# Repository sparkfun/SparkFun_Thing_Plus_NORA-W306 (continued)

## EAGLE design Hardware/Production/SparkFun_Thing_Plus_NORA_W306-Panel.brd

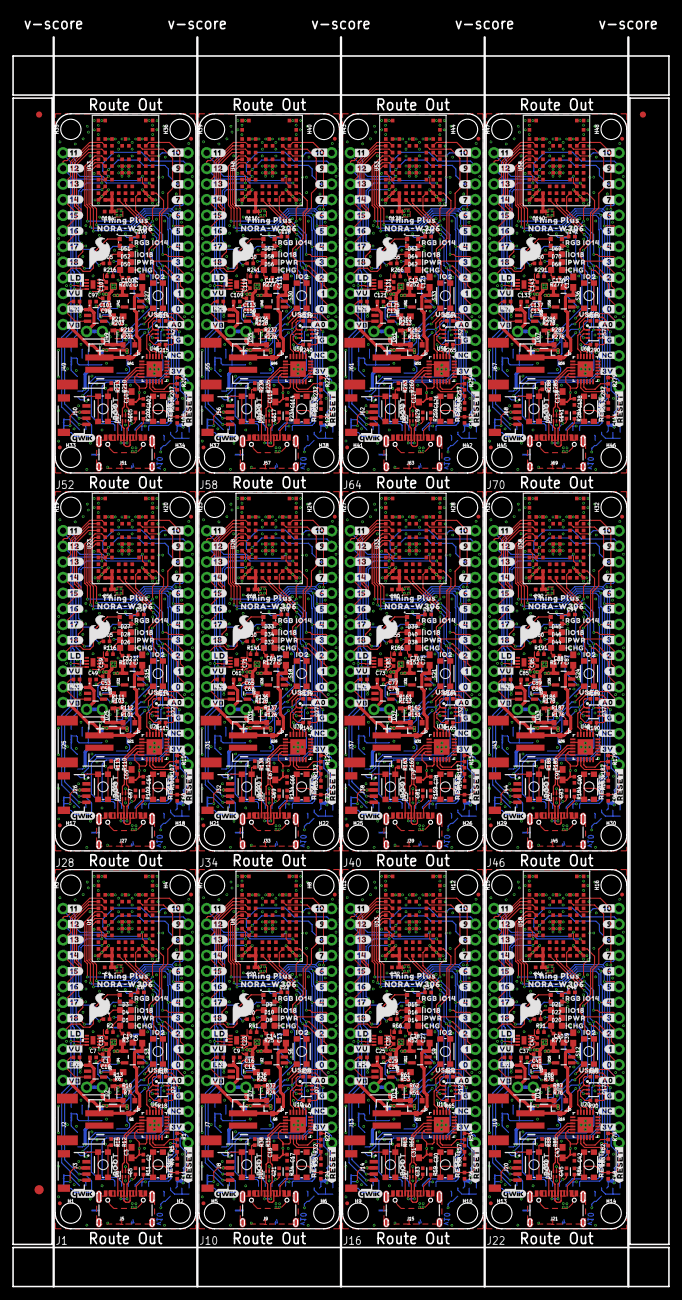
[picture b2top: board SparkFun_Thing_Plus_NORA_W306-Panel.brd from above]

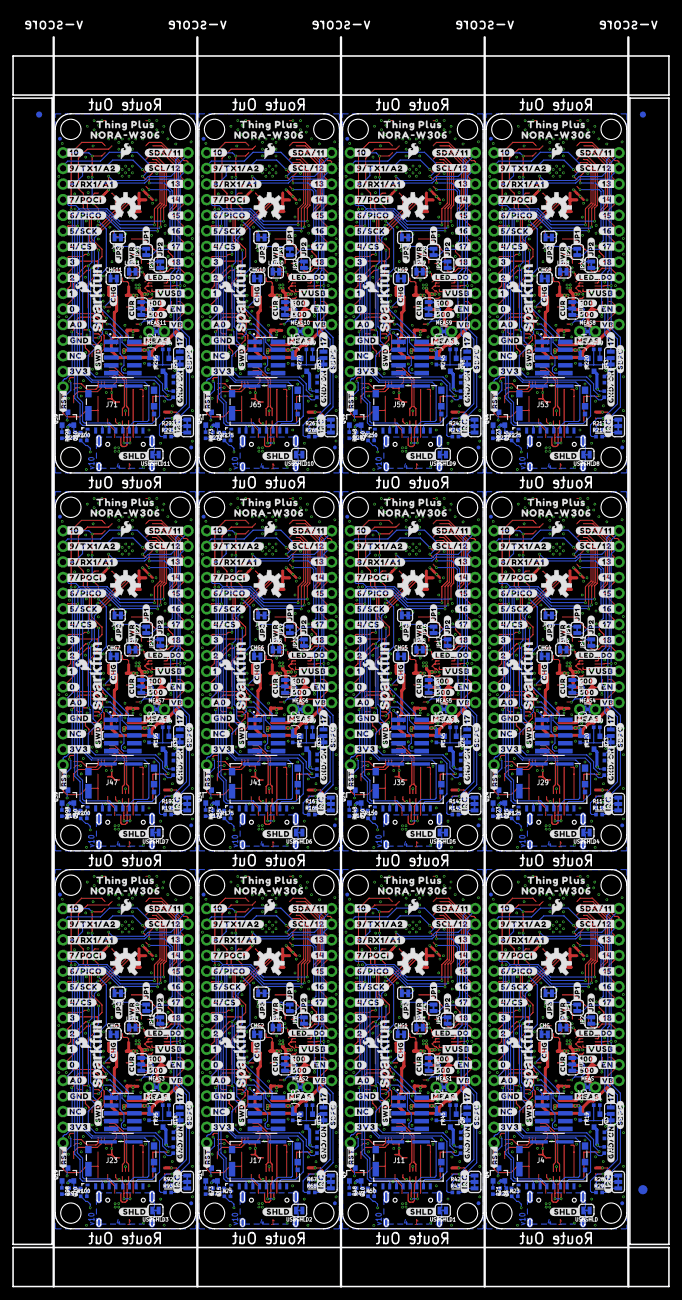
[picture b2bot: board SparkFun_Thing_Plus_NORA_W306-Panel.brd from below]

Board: 4 copper layers, 106.7 x 203.2 mm, 2022 parts (891 on the bottom side), 792 nets.

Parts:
C1, C4, C5, C16, C20, C21, C29, C32, C33, C41, C44, C45, C53, C56, C57, C65, C68, C69, C77, C80, C81, C89, C92, C93, C101, C104, C105, C113, C116, C117, C125, C128, C129, C137, C140, C141: 10uF; 0402-TIGHT
C2, C8, C11, C15, C17, C22, C23, C24, C30, C34, C35, C36, C42, C46, C47, C48, C54, C58, C59, C60, C66, C70, C71, C72, C78, C82, C83, C84, C90, C94, C95, C96, C102, C106, C107, C108, C114, C118, C119, C120, C126, C130, C131, C132, C138, C142, C143, C144: 0.1uF; 0402-TIGHT
C3, C6, C13, C14, C18, C19, C27, C28, C31, C39, C40, C43, C51, C52, C55, C63, C64, C67, C75, C76, C79, C87, C88, C91, C99, C100, C103, C111, C112, C115, C123, C124, C127, C135, C136, C139: 4.7uF; 0603
C7, C9, C10, C12, C25, C26, C37, C38, C49, C50, C61, C62, C73, C74, C85, C86, C97, C98, C109, C110, C121, C122, C133, C134: 1.0uF; 0402-TIGHT
CHG, CHG1, CHG2, CHG3, CHG4, CHG5, CHG6, CHG7, CHG8, CHG9, CHG10, CHG11: SMT-JUMPER_2_NC_TRACE_SILK
CUR, CUR1, CUR2, CUR3, CUR4, CUR5, CUR6, CUR7, CUR8, CUR9, CUR10, CUR11: SMT-JUMPER_3_1-NC_TRACE_SILK
D1, D8, D14, D20, D26, D32, D38, D44, D50, D56, D62, D68: Yellow; LED-0603
D2, D7, D13, D19, D25, D31, D37, D43, D49, D55, D61, D67: 1A/23V/620mV; SOD-323
D3, D9, D15, D21, D27, D33, D39, D45, D51, D57, D63, D69: BLUE; LED-0603
D4, D10, D16, D22, D28, D34, D40, D46, D52, D58, D64, D70: RED; LED-0603
D5, D12, D18, D24, D30, D36, D42, D48, D54, D60, D66, D72: WS2812; WS2812-2020
D6, D11, D17, D23, D29, D35, D41, D47, D53, D59, D65, D71: PRTR5V0U2F; SOT886
E$1, E$2, E$3, E$4: FIDUCIAL-1X2
E$5, E$6: FIDUCIAL-1.5X3
FD1, FD2, FD3, FD4, FD5, FD6, FD7, FD8, FD9, FD10, FD11, FD12, FD13, FD14, FD15, FD16, FD17, FD18, FD19, FD20, FD21, FD22, FD23, FD24, FD25, FD26, FD27, FD28, FD29, FD30, FD31, FD32, FD33, FD34, FD35, FD36, FD37, FD38, FD39, FD40, FD41, FD42, FD43, FD44, FD45, FD46, FD47, FD48: FIDUCIALUFIDUCIAL; FIDUCIAL-MICRO
H1, H2, H3, H4, H5, H6, H7, H8, H9, H10, H11, H12, H13, H14, H15, H16, H17, H18, H19, H20, H21, H22, H23, H24, H25, H26, H27, H28, H29, H30, H31, H32, H33, H34, H35, H36, H37, H38, H39, H40, H41, H42, H43, H44, H45, H46, H47, H48: STAND-OFF
I2C, I2C1, I2C2, I2C3, I2C4, I2C5, I2C6, I2C7, I2C8, I2C9, I2C10, I2C11: JUMPER-SMT_3_2-NC_TRACE_SILK; SMT-JUMPER_3_2-NC_TRACE_SILK
J1, J10, J16, J22, J28, J34, J40, J46, J52, J58, J64, J70: THING_PLUS_LOGICAL; THING_PLUS
J2, J7, J13, J19, J25, J31, J37, J43, J49, J55, J61, J67: LiPo; JST-2-SMD
J3, J8, J14, J20, J26, J32, J38, J44, J50, J56, J62, J68: QWIIC_RIGHT_ANGLE; JST04_1MM_RA
J4, J11, J17, J23, J29, J35, J41, J47, J53, J59, J65, J71: SDFRICTION; MICROSD_TINY
J5, J9, J15, J21, J27, J33, J39, J45, J51, J57, J63, J69: USB-C; USB-C-16P-4LAYER-ISOLATED
J6, J12, J18, J24, J30, J36, J42, J48, J54, J60, J66, J72: SWD (DNP); 2X5-SMD-UNSHROUDED_DNP_NO_PASTE
JP1, JP2, JP3, JP4, JP5, JP6, JP7, JP8, JP9, JP10, JP11, JP12, JP13, JP14, JP15, JP16, JP17, JP18, JP19, JP20, JP21, JP22, JP23, JP24, JP25, JP26, JP27, JP28, JP29, JP30, JP31, JP32, JP33, JP34, JP35, JP36: SMT-JUMPER_2_NC_TRACE_SILK
LED, LED1, LED2, LED3, LED4, LED5, LED6, LED7, LED8, LED9, LED10, LED11: SMT-JUMPER_2_NC_TRACE_SILK
LOGO1, LOGO2, LOGO7, LOGO10, LOGO13, LOGO16, LOGO19, LOGO22, LOGO25, LOGO28, LOGO31, LOGO34: OSHW-LOGOM; OSHW-LOGO-M
LOGO3, LOGO5, LOGO9, LOGO12, LOGO15, LOGO18, LOGO21, LOGO24, LOGO27, LOGO30, LOGO33, LOGO36: SFE_LOGO_NAME_FLAME.1_INCH; SFE_LOGO_NAME_FLAME_.1
LOGO4, LOGO6, LOGO8, LOGO11, LOGO14, LOGO17, LOGO20, LOGO23, LOGO26, LOGO29, LOGO32, LOGO35: QWIIC_LOGO_4MM; QWIIC_4MM
MEAS, MEAS1, MEAS2, MEAS3, MEAS4, MEAS5, MEAS6, MEAS7, MEAS8, MEAS9, MEAS10, MEAS11: COMBO-JUMPER_2_NC_TRACE
Q1, Q3, Q4, Q6, Q8, Q9, Q11, Q13, Q14, Q16, Q18, Q19, Q21, Q23, Q24, Q26, Q28, Q29, Q31, Q33, Q34, Q36, Q38, Q39, Q41, Q43, Q44, Q46, Q48, Q49, Q51, Q53, Q54, Q56, Q58, Q59: 20V/4.2A/52mΩ/1.4W; SOT23-3
Q2, Q7, Q12, Q17, Q22, Q27, Q32, Q37, Q42, Q47, Q52, Q57: MBT3904DW1T1; SC70-6
Q5, Q10, Q15, Q20, Q25, Q30, Q35, Q40, Q45, Q50, Q55, Q60: 20V/0.2A/8MHz/1.2Ω/1Vth; SOT-416FL
R1, R13, R17, R18, R27, R36, R39, R40, R54, R61, R64, R65, R79, R86, R89, R90, R104, R111, R114, R115, R129, R136, R139, R140, R154, R161, R164, R165, R179, R186, R189, R190, R204, R211, R214, R215, R229, R236, R239, R240, R254, R261, R264, R265, R279, R286, R289, R290: 10k; 0402-TIGHT
R2, R3, R4, R25, R30, R41, R52, R55, R66, R77, R80, R91, R102, R105, R116, R127, R130, R141, R152, R155, R166, R177, R180, R191, R202, R205, R216, R227, R230, R241, R252, R255, R266, R277, R280, R291: 4.7k; 0402-TIGHT
R5, R32, R57, R82, R107, R132, R157, R182, R207, R232, R257, R282: 22k; 0402-TIGHT
R6, R26, R53, R78, R103, R128, R153, R178, R203, R228, R253, R278: 2.0k; 0603
R7, R8, R16, R19, R20, R24, R31, R45, R46, R47, R51, R56, R70, R71, R72, R76, R81, R95, R96, R97, R101, R106, R120, R121, R122, R126, R131, R145, R146, R147, R151, R156, R170, R171, R172, R176, R181, R195, R196, R197, R201, R206, R220, R221, R222, R226, R231, R245, R246, R247, R251, R256, R270, R271, R272, R276, R281, R295, R296, R297: 100k; 0402-TIGHT
R9, R33, R58, R83, R108, R133, R158, R183, R208, R233, R258, R283: 33k; 0402-TIGHT
R10, R14, R21, R23, R37, R44, R48, R50, R62, R69, R73, R75, R87, R94, R98, R100, R112, R119, R123, R125, R137, R144, R148, R150, R162, R169, R173, R175, R187, R194, R198, R200, R212, R219, R223, R225, R237, R244, R248, R250, R262, R269, R273, R275, R287, R294, R298, R300: 100; 0402-TIGHT
R11, R12, R34, R35, R59, R60, R84, R85, R109, R110, R134, R135, R159, R160, R184, R185, R209, R210, R234, R235, R259, R260, R284, R285: 5.1k; 0402-TIGHT
R15, R22, R38, R49, R63, R74, R88, R99, R113, R124, R138, R149, R163, R174, R188, R199, R213, R224, R238, R249, R263, R274, R288, R299: 1k; 0402-TIGHT
R28, R29, R42, R43, R67, R68, R92, R93, R117, R118, R142, R143, R167, R168, R192, R193, R217, R218, R242, R243, R267, R268, R292, R293: 2.2k; 0402-TIGHT
S1, S4, S7, S10, S13, S16, S19, S22, S25, S28, S31, S34: RESET; TACTILE_SWITCH_SMD_4.6X2.8MM
S2, S5, S8, S11, S14, S17, S20, S23, S26, S29, S32, S35: BOOT; TACTILE_SWITCH_SMD_4.6X2.8MM
S3, S6, S9, S12, S15, S18, S21, S24, S27, S30, S33, S36: USER; TACTILE_SWITCH_SMD_4.6X2.8MM
SDPC, SDPC1, SDPC2, SDPC3, SDPC4, SDPC5, SDPC6, SDPC7, SDPC8, SDPC9, SDPC10, SDPC11: SMT-JUMPER_3_1-NC_TRACE_SILK
U1, U8, U13, U18, U23, U28, U33, U38, U43, U48, U53, U58: UBLOX_NORA_W306; UBLOX-NORA-W3
U2, U4, U11, U16, U21, U26, U31, U36, U41, U46, U51, U56: MCP73831; SOT23-5
U3, U7, U12, U17, U22, U27, U32, U37, U42, U47, U52, U57: XC6222B331MR-G; SOT23-5
U5, U9, U14, U19, U24, U29, U34, U39, U44, U49, U54, U59: MAX17048; DFN-8
U6, U10, U15, U20, U25, U30, U35, U40, U45, U50, U55, U60: CP2102N; QFN24
U$1, U$22, U$132, U$161, U$217, U$246, U$302, U$331, U$387, U$416, U$472, U$501, U$557, U$586, U$642, U$671, U$727, U$756, U$812, U$841, U$897, U$926, U$982, U$1011: #17#11
U$2, U$92, U$177, U$262, U$347, U$432, U$517, U$602, U$687, U$772, U$857, U$942: BOOT0
U$3, U$157, U$242, U$327, U$412, U$497, U$582, U$667, U$752, U$837, U$922, U$1007: #MEAS#1714141838
U$4, U$166, U$251, U$336, U$421, U$506, U$591, U$676, U$761, U$846, U$931, U$1016: IO180
U$5, U$94, U$179, U$264, U$349, U$434, U$519, U$604, U$689, U$774, U$859, U$944: NORA#W3060
U$6, U$162, U$247, U$332, U$417, U$502, U$587, U$672, U$757, U$842, U$927, U$1012: ##RST##23061714141845
U$7, U$123, U$208, U$293, U$378, U$463, U$548, U$633, U$718, U$803, U$888, U$973: USER0
U$8, U$95, U$180, U$265, U$350, U$435, U$520, U$605, U$690, U$775, U$860, U$945: SFE_LOGO_FLAME_.2
U$9, U$167, U$252, U$337, U$422, U$507, U$592, U$677, U$762, U$847, U$932, U$1017: IO20
U$10, U$160, U$245, U$330, U$415, U$500, U$585, U$670, U$755, U$840, U$925, U$1010: #GND#ON#3061714141842
U$11, U$170, U$255, U$340, U$425, U$510, U$595, U$680, U$765, U$850, U$935, U$1020: #SDPC#0
U$12, U$96, U$181, U$266, U$351, U$436, U$521, U$606, U$691, U$776, U$861, U$946: #A0#1
U$13, U$150, U$235, U$320, U$405, U$490, U$575, U$660, U$745, U$830, U$915, U$1000: #SDA#11#28
U$14, U$152, U$237, U$322, U$407, U$492, U$577, U$662, U$747, U$832, U$917, U$1002: #17#28
U$15, U$97, U$182, U$267, U$352, U$437, U$522, U$607, U$692, U$777, U$862, U$947: #0#4
U$16, U$98, U$183, U$268, U$353, U$438, U$523, U$608, U$693, U$778, U$863, U$948: #1#4
U$17, U$151, U$236, U$321, U$406, U$491, U$576, U$661, U$746, U$831, U$916, U$1001: #SCL#12#28
U$18, U$153, U$238, U$323, U$408, U$493, U$578, U$663, U$748, U$833, U$918, U$1003: #18#28
U$19, U$154, U$239, U$324, U$409, U$494, U$579, U$664, U$749, U$834, U$919, U$1004: SFE_LOGO_FLAME_.1
U$20, U$155, U$240, U$325, U$410, U$495, U$580, U$665, U$750, U$835, U$920, U$1005: #LD#29
U$21, U$168, U$253, U$338, U$423, U$508, U$593, U$678, U$763, U$848, U$933, U$1018: RGB_IO140
U$23, U$93, U$178, U$263, U$348, U$433, U$518, U$603, U$688, U$773, U$858, U$943: PWR0
U$24, U$169, U$254, U$339, U$424, U$509, U$594, U$679, U$764, U$849, U$934, U$1019: #CUR#0
U$25, U$158, U$243, U$328, U$413, U$498, U$583, U$668, U$753, U$838, U$923, U$1008: THING_PLUS1714141839
U$26, U$77, U$139, U$156, U$224, U$241, U$309, U$326, U$394, U$411, U$479, U$496, U$564, U$581, U$649, U$666, U$734, U$751, U$819, U$836, U$904, U$921, U$989, U$1006: #VB26
U$27, U$78, U$171, U$256, U$341, U$426, U$511, U$596, U$681, U$766, U$851, U$936: CHG0
U$28, U$159, U$244, U$329, U$414, U$499, U$584, U$669, U$754, U$839, U$924, U$1009: NORA#W3061714141840
U$29, U$79, U$172, U$257, U$342, U$427, U$512, U$597, U$682, U$767, U$852, U$937: RESET0
U$30, U$99, U$184, U$269, U$354, U$439, U$524, U$609, U$694, U$779, U$864, U$949: #13#13
U$31, U$100, U$185, U$270, U$355, U$440, U$525, U$610, U$695, U$780, U$865, U$950: #14#14
U$32, U$101, U$186, U$271, U$356, U$441, U$526, U$611, U$696, U$781, U$866, U$951: #15#15
U$33, U$102, U$187, U$272, U$357, U$442, U$527, U$612, U$697, U$782, U$867, U$952: #16#16
U$34, U$41, U$173, U$258, U$343, U$428, U$513, U$598, U$683, U$768, U$853, U$938: #VUSB#0
U$35, U$133, U$218, U$303, U$388, U$473, U$558, U$643, U$728, U$813, U$898, U$983: #18#18
U$36, U$103, U$188, U$273, U$358, U$443, U$528, U$613, U$698, U$783, U$868, U$953: #11#91420
U$37, U$104, U$189, U$274, U$359, U$444, U$529, U$614, U$699, U$784, U$869, U$954: #12#91420
U$38, U$105, U$190, U$275, U$360, U$445, U$530, U$615, U$700, U$785, U$870, U$955: #13#91420
U$39, U$106, U$191, U$276, U$361, U$446, U$531, U$616, U$701, U$786, U$871, U$956: #14#91420
U$40, U$107, U$192, U$277, U$362, U$447, U$532, U$617, U$702, U$787, U$872, U$957: #15#91420
U$42, U$163, U$248, U$333, U$418, U$503, U$588, U$673, U$758, U$843, U$928, U$1013: #JP3#23061714141846
U$43, U$59, U$174, U$259, U$344, U$429, U$514, U$599, U$684, U$769, U$854, U$939: #EN#0
U$44, U$108, U$193, U$278, U$363, U$448, U$533, U$618, U$703, U$788, U$873, U$958: #16#91420
U$45, U$89, U$175, U$260, U$345, U$430, U$515, U$600, U$685, U$770, U$855, U$940: #3V3#0
U$46, U$124, U$209, U$294, U$379, U$464, U$549, U$634, U$719, U$804, U$889, U$974: #NC#2
U$47, U$122, U$207, U$292, U$377, U$462, U$547, U$632, U$717, U$802, U$887, U$972: #A0#18
U$48, U$109, U$194, U$279, U$364, U$449, U$534, U$619, U$704, U$789, U$874, U$959: #8#91421
U$49, U$110, U$195, U$280, U$365, U$450, U$535, U$620, U$705, U$790, U$875, U$960: #7#8
U$50, U$111, U$196, U$281, U$366, U$451, U$536, U$621, U$706, U$791, U$876, U$961: #6#8
U$51, U$112, U$197, U$282, U$367, U$452, U$537, U$622, U$707, U$792, U$877, U$962: #5#8
U$52, U$113, U$198, U$283, U$368, U$453, U$538, U$623, U$708, U$793, U$878, U$963: #4#8
U$53, U$114, U$199, U$284, U$369, U$454, U$539, U$624, U$709, U$794, U$879, U$964: #3#8
U$54, U$115, U$200, U$285, U$370, U$455, U$540, U$625, U$710, U$795, U$880, U$965: #2#8
U$55, U$116, U$201, U$286, U$371, U$456, U$541, U$626, U$711, U$796, U$881, U$966: #1#8
U$56, U$117, U$202, U$287, U$372, U$457, U$542, U$627, U$712, U$797, U$882, U$967: #0#8
U$57, U$137, U$222, U$307, U$392, U$477, U$562, U$647, U$732, U$817, U$902, U$987: #3V#23
U$58, U$127, U$212, U$297, U$382, U$467, U$552, U$637, U$722, U$807, U$892, U$977: #JP2#0
U$60, U$126, U$211, U$296, U$381, U$466, U$551, U$636, U$721, U$806, U$891, U$976: #SWD#501
U$61, U$164, U$249, U$334, U$419, U$504, U$589, U$674, U$759, U$844, U$929, U$1014: #100#23061714141846
U$62, U$90, U$176, U$261, U$346, U$431, U$516, U$601, U$686, U$771, U$856, U$941: THING_PLUS_0
U$63, U$118, U$203, U$288, U$373, U$458, U$543, U$628, U$713, U$798, U$883, U$968: #SHLD#9
U$64, U$119, U$204, U$289, U$374, U$459, U$544, U$629, U$714, U$799, U$884, U$969: #GND#10
U$65, U$129, U$214, U$299, U$384, U$469, U$554, U$639, U$724, U$809, U$894, U$979: #JP1#0
U$66, U$121, U$206, U$291, U$376, U$461, U$546, U$631, U$716, U$801, U$886, U$971: #PWR#14
U$67, U$120, U$205, U$290, U$375, U$460, U$545, U$630, U$715, U$800, U$885, U$970: #CHG#13
U$68, U$134, U$219, U$304, U$389, U$474, U$559, U$644, U$729, U$814, U$899, U$984: ##RESET##19
U$69, U$135, U$220, U$305, U$390, U$475, U$560, U$645, U$730, U$815, U$900, U$985: #NC#21
U$70, U$130, U$215, U$300, U$385, U$470, U$555, U$640, U$725, U$810, U$895, U$980: #9#10
U$71, U$128, U$213, U$298, U$383, U$468, U$553, U$638, U$723, U$808, U$893, U$978: #LED_DO#0
U$72, U$125, U$210, U$295, U$380, U$465, U$550, U$635, U$720, U$805, U$890, U$975: #I2C#3
U$73, U$165, U$250, U$335, U$420, U$505, U$590, U$675, U$760, U$845, U$930, U$1015: #500#23061714141846
U$74, U$131, U$216, U$301, U$386, U$471, U$556, U$641, U$726, U$811, U$896, U$981: #10#11
U$75, U$136, U$221, U$306, U$391, U$476, U$561, U$646, U$731, U$816, U$901, U$986: #G#22
U$76, U$138, U$223, U$308, U$393, U$478, U$563, U$648, U$733, U$818, U$903, U$988: #VU#23
U$80, U$140, U$225, U$310, U$395, U$480, U$565, U$650, U$735, U$820, U$905, U$990: #EN#27
U$81, U$141, U$226, U$311, U$396, U$481, U$566, U$651, U$736, U$821, U$906, U$991: #2#28
U$82, U$142, U$227, U$312, U$397, U$482, U$567, U$652, U$737, U$822, U$907, U$992: #3#28
U$83, U$143, U$228, U$313, U$398, U$483, U$568, U$653, U$738, U$823, U$908, U$993: #4#CS#28
U$84, U$144, U$229, U$314, U$399, U$484, U$569, U$654, U$739, U$824, U$909, U$994: #5#SCK#28
U$85, U$145, U$230, U$315, U$400, U$485, U$570, U$655, U$740, U$825, U$910, U$995: #6#PICO#28
U$86, U$146, U$231, U$316, U$401, U$486, U$571, U$656, U$741, U$826, U$911, U$996: #7#POCI#28
U$87, U$148, U$233, U$318, U$403, U$488, U$573, U$658, U$743, U$828, U$913, U$998: #9#TX1#A2#28
U$88, U$147, U$232, U$317, U$402, U$487, U$572, U$657, U$742, U$827, U$912, U$997: #8#RX1#A1#28
U$91, U$149, U$234, U$319, U$404, U$489, U$574, U$659, U$744, U$829, U$914, U$999: #10#28
USBSHLD, USBSHLD1, USBSHLD2, USBSHLD3, USBSHLD4, USBSHLD5, USBSHLD6, USBSHLD7, USBSHLD8, USBSHLD9, USBSHLD10, USBSHLD11: SMT-JUMPER_2_NC_TRACE_SILK

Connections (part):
3.3V: C1.1, C4.1, C10.1, I2C.2, J1.27, J3.2, J6.1, JP3.1, LED.1, Q3.2, Q4.2, R19.1, R20.1, U1.A7, U1.A8, U1.B7, U3.5
3.3V1: C12.1, C16.1, C20.1, I2C1.2, J8.2, J10.27, J12.1, JP6.1, LED1.1, Q8.2, Q9.2, R45.1, R47.1, U7.5, U8.A7, U8.A8, U8.B7
3.3V2: C26.1, C29.1, C32.1, I2C2.2, J14.2, J16.27, J18.1, JP9.1, LED2.1, Q13.2, Q14.2, R70.1, R72.1, U12.5, U13.A7, U13.A8, U13.B7
3.3V3: C38.1, C41.1, C44.1, I2C3.2, J20.2, J22.27, J24.1, JP12.1, LED3.1, Q18.2, Q19.2, R95.1, R97.1, U17.5, U18.A7, U18.A8, U18.B7
3.3V4: C50.1, C53.1, C56.1, I2C4.2, J26.2, J28.27, J30.1, JP15.1, LED4.1, Q23.2, Q24.2, R120.1, R122.1, U22.5, U23.A7, U23.A8, U23.B7
3.3V5: C62.1, C65.1, C68.1, I2C5.2, J32.2, J34.27, J36.1, JP18.1, LED5.1, Q28.2, Q29.2, R145.1, R147.1, U27.5, U28.A7, U28.A8, U28.B7
3.3V6: C74.1, C77.1, C80.1, I2C6.2, J38.2, J40.27, J42.1, JP21.1, LED6.1, Q33.2, Q34.2, R170.1, R172.1, U32.5, U33.A7, U33.A8, U33.B7
3.3V7: C86.1, C89.1, C92.1, I2C7.2, J44.2, J46.27, J48.1, JP24.1, LED7.1, Q38.2, Q39.2, R195.1, R197.1, U37.5, U38.A7, U38.A8, U38.B7
3.3V8: C98.1, C101.1, C104.1, I2C8.2, J50.2, J52.27, J54.1, JP27.1, LED8.1, Q43.2, Q44.2, R220.1, R222.1, U42.5, U43.A7, U43.A8, U43.B7
3.3V9: C110.1, C113.1, C116.1, I2C9.2, J56.2, J58.27, J60.1, JP30.1, LED9.1, Q48.2, Q49.2, R245.1, R247.1, U47.5, U48.A7, U48.A8, U48.B7
3.3V10: C122.1, C125.1, C128.1, I2C10.2, J62.2, J64.27, J66.1, JP33.1, LED10.1, Q53.2, Q54.2, R270.1, R272.1, U52.5, U53.A7, U53.A8, U53.B7
3.3V11: C134.1, C137.1, C140.1, I2C11.2, J68.2, J70.27, J72.1, JP36.1, LED11.1, Q58.2, Q59.2, R295.1, R297.1, U57.5, U58.A7, U58.A8, U58.B7
!RESET!: C11.1, J1.28, J6.10, Q2.3, S1.1, S1.2, U1.J3
!RESET!1: C24.1, J10.28, J12.10, Q7.3, S4.1, S4.2, U8.J3
!RESET!2: C36.1, J16.28, J18.10, Q12.3, S7.1, S7.2, U13.J3
!RESET!3: C48.1, J22.28, J24.10, Q17.3, S10.1, S10.2, U18.J3
!RESET!4: C60.1, J28.28, J30.10, Q22.3, S13.1, S13.2, U23.J3
!RESET!5: C72.1, J34.28, J36.10, Q27.3, S16.1, S16.2, U28.J3
!RESET!6: C84.1, J40.28, J42.10, Q32.3, S19.1, S19.2, U33.J3
!RESET!7: C96.1, J46.28, J48.10, Q37.3, S22.1, S22.2, U38.J3
!RESET!8: C108.1, J52.28, J54.10, Q42.3, S25.1, S25.2, U43.J3
!RESET!9: C120.1, J58.28, J60.10, Q47.3, S28.1, S28.2, U48.J3
!RESET!10: C132.1, J64.28, J66.10, Q52.3, S31.1, S31.2, U53.J3
!RESET!11: C144.1, J70.28, J72.10, Q57.3, S34.1, S34.2, U58.J3
CC1: J5.A5, R12.2
CC2: J5.B5, R11.2
CC3: J9.B5, R34.2
CC4: J9.A5, R35.2
CC5: J15.B5, R59.2
CC6: J15.A5, R60.2
CC7: J21.B5, R84.2
CC8: J21.A5, R85.2
CC9: J27.B5, R109.2
CC10: J27.A5, R110.2
CC11: J33.B5, R134.2
CC12: J33.A5, R135.2
CC13: J39.B5, R159.2
CC14: J39.A5, R160.2
CC15: J45.B5, R184.2
CC16: J45.A5, R185.2
CC17: J51.B5, R209.2
CC18: J51.A5, R210.2
CC19: J57.B5, R234.2
CC20: J57.A5, R235.2
CC21: J63.B5, R259.2
CC22: J63.A5, R260.2
CC23: J69.B5, R284.2
CC24: J69.A5, R285.2
CHG: CHG.2, U4.1
CHG1: CHG1.2, U2.1
CHG2: CHG2.2, U11.1
CHG3: CHG3.2, U16.1
CHG4: CHG4.2, U21.1
CHG5: CHG5.2, U26.1
CHG6: CHG6.2, U31.1
CHG7: CHG7.2, U36.1
CHG8: CHG8.2, U41.1
CHG9: CHG9.2, U46.1
CHG10: CHG10.2, U51.1
CHG11: CHG11.2, U56.1
DTR: Q2.1, R17.1, U6.23
DTR1: Q7.1, R39.1, U10.23
DTR2: Q12.1, R64.1, U15.23
DTR3: Q17.1, R89.1, U20.23
DTR4: Q22.1, R114.1, U25.23
DTR5: Q27.1, R139.1, U30.23
DTR6: Q32.1, R164.1, U35.23
DTR7: Q37.1, R189.1, U40.23
DTR8: Q42.1, R214.1, U45.23
DTR9: Q47.1, R239.1, U50.23
DTR10: Q52.1, R264.1, U55.23
DTR11: Q57.1, R289.1, U60.23
EN: J1.11, R8.2, U3.3
EN1: J10.11, R31.2, U7.3
EN2: J16.11, R56.2, U12.3
EN3: J22.11, R81.2, U17.3
EN4: J28.11, R106.2, U22.3
EN5: J34.11, R131.2, U27.3
EN6: J40.11, R156.2, U32.3
EN7: J46.11, R181.2, U37.3
EN8: J52.11, R206.2, U42.3
EN9: J58.11, R231.2, U47.3
EN10: J64.11, R256.2, U52.3
EN11: J70.11, R281.2, U57.3
GND: C1.2, C2.2, C3.2, C4.2, C5.2, C6.2, C7.2, C8.2, C10.2, C11.2, C15.2, C19.2, D3.C, D4.C, D5.GND, D6.2, J1.25, J2.1, J3.1, J4.6, J4.GND1, J4.GND2, J4.GND3, J4.GND4, J4.GND5, J4.GND6, J5.GND, J5.GND2, J6.3, J6.5, J6.9, Q5.2, R6.1, R7.1, R9.1, R11.1, R12.1, R13.2, R15.1, R22.2, S1.3, S1.4, S3.3, S3.4, U1.A1, U1.A9, U1.B2, U1.B8, U1.E4, U1.E5, U1.F4, U1.F5, U1.K2, U1.K3, U1.K5, U1.K7, U1.K8, U1.L1, U1.L9, U1.M1, U1.M2, U1.M8, U1.M9, U3.2, U4.2, U5.1, U5.4, U5.6, U5.9, U6.2, U6.PAD, USBSHLD.1
GND1: C9.2, C12.2, C13.2, C14.2, C16.2, C17.2, C18.2, C20.2, C21.2, C22.2, C23.2, C24.2, D9.C, D10.C, D11.2, D12.GND, J7.1, J8.1, J9.GND, J9.GND2, J10.25, J11.6, J11.GND1, J11.GND2, J11.GND3, J11.GND4, J11.GND5, J11.GND6, J12.3, J12.5, J12.9, Q10.2, R24.1, R26.1, R33.1, R34.1, R35.1, R36.2, R38.1, R49.2, S4.3, S4.4, S6.3, S6.4, U2.2, U7.2, U8.A1, U8.A9, U8.B2, U8.B8, U8.E4, U8.E5, U8.F4, U8.F5, U8.K2, U8.K3, U8.K5, U8.K7, U8.K8, U8.L1, U8.L9, U8.M1, U8.M2, U8.M8, U8.M9, U9.1, U9.4, U9.6, U9.9, U10.2, U10.PAD, USBSHLD1.1
GND2: C25.2, C26.2, C27.2, C28.2, C29.2, C30.2, C31.2, C32.2, C33.2, C34.2, C35.2, C36.2, D15.C, D16.C, D17.2, D18.GND, J13.1, J14.1, J15.GND, J15.GND2, J16.25, J17.6, J17.GND1, J17.GND2, J17.GND3, J17.GND4, J17.GND5, J17.GND6, J18.3, J18.5, J18.9, Q15.2, R51.1, R53.1, R58.1, R59.1, R60.1, R61.2, R63.1, R74.2, S7.3, S7.4, S9.3, S9.4, U11.2, U12.2, U13.A1, U13.A9, U13.B2, U13.B8, U13.E4, U13.E5, U13.F4, U13.F5, U13.K2, U13.K3, U13.K5, U13.K7, U13.K8, U13.L1, U13.L9, U13.M1, U13.M2, U13.M8, U13.M9, U14.1, U14.4, U14.6, U14.9, U15.2, U15.PAD, USBSHLD2.1
GND3: C37.2, C38.2, C39.2, C40.2, C41.2, C42.2, C43.2, C44.2, C45.2, C46.2, C47.2, C48.2, D21.C, D22.C, D23.2, D24.GND, J19.1, J20.1, J21.GND, J21.GND2, J22.25, J23.6, J23.GND1, J23.GND2, J23.GND3, J23.GND4, J23.GND5, J23.GND6, J24.3, J24.5, J24.9, Q20.2, R76.1, R78.1, R83.1, R84.1, R85.1, R86.2, R88.1, R99.2, S10.3, S10.4, S12.3, S12.4, U16.2, U17.2, U18.A1, U18.A9, U18.B2, U18.B8, U18.E4, U18.E5, U18.F4, U18.F5, U18.K2, U18.K3, U18.K5, U18.K7, U18.K8, U18.L1, U18.L9, U18.M1, U18.M2, U18.M8, U18.M9, U19.1, U19.4, U19.6, U19.9, U20.2, U20.PAD, USBSHLD3.1
GND4: C49.2, C50.2, C51.2, C52.2, C53.2, C54.2, C55.2, C56.2, C57.2, C58.2, C59.2, C60.2, D27.C, D28.C, D29.2, D30.GND, J25.1, J26.1, J27.GND, J27.GND2, J28.25, J29.6, J29.GND1, J29.GND2, J29.GND3, J29.GND4, J29.GND5, J29.GND6, J30.3, J30.5, J30.9, Q25.2, R101.1, R103.1, R108.1, R109.1, R110.1, R111.2, R113.1, R124.2, S13.3, S13.4, S15.3, S15.4, U21.2, U22.2, U23.A1, U23.A9, U23.B2, U23.B8, U23.E4, U23.E5, U23.F4, U23.F5, U23.K2, U23.K3, U23.K5, U23.K7, U23.K8, U23.L1, U23.L9, U23.M1, U23.M2, U23.M8, U23.M9, U24.1, U24.4, U24.6, U24.9, U25.2, U25.PAD, USBSHLD4.1
GND5: C61.2, C62.2, C63.2, C64.2, C65.2, C66.2, C67.2, C68.2, C69.2, C70.2, C71.2, C72.2, D33.C, D34.C, D35.2, D36.GND, J31.1, J32.1, J33.GND, J33.GND2, J34.25, J35.6, J35.GND1, J35.GND2, J35.GND3, J35.GND4, J35.GND5, J35.GND6, J36.3, J36.5, J36.9, Q30.2, R126.1, R128.1, R133.1, R134.1, R135.1, R136.2, R138.1, R149.2, S16.3, S16.4, S18.3, S18.4, U26.2, U27.2, U28.A1, U28.A9, U28.B2, U28.B8, U28.E4, U28.E5, U28.F4, U28.F5, U28.K2, U28.K3, U28.K5, U28.K7, U28.K8, U28.L1, U28.L9, U28.M1, U28.M2, U28.M8, U28.M9, U29.1, U29.4, U29.6, U29.9, U30.2, U30.PAD, USBSHLD5.1
GND6: C73.2, C74.2, C75.2, C76.2, C77.2, C78.2, C79.2, C80.2, C81.2, C82.2, C83.2, C84.2, D39.C, D40.C, D41.2, D42.GND, J37.1, J38.1, J39.GND, J39.GND2, J40.25, J41.6, J41.GND1, J41.GND2, J41.GND3, J41.GND4, J41.GND5, J41.GND6, J42.3, J42.5, J42.9, Q35.2, R151.1, R153.1, R158.1, R159.1, R160.1, R161.2, R163.1, R174.2, S19.3, S19.4, S21.3, S21.4, U31.2, U32.2, U33.A1, U33.A9, U33.B2, U33.B8, U33.E4, U33.E5, U33.F4, U33.F5, U33.K2, U33.K3, U33.K5, U33.K7, U33.K8, U33.L1, U33.L9, U33.M1, U33.M2, U33.M8, U33.M9, U34.1, U34.4, U34.6, U34.9, U35.2, U35.PAD, USBSHLD6.1
GND7: C85.2, C86.2, C87.2, C88.2, C89.2, C90.2, C91.2, C92.2, C93.2, C94.2, C95.2, C96.2, D45.C, D46.C, D47.2, D48.GND, J43.1, J44.1, J45.GND, J45.GND2, J46.25, J47.6, J47.GND1, J47.GND2, J47.GND3, J47.GND4, J47.GND5, J47.GND6, J48.3, J48.5, J48.9, Q40.2, R176.1, R178.1, R183.1, R184.1, R185.1, R186.2, R188.1, R199.2, S22.3, S22.4, S24.3, S24.4, U36.2, U37.2, U38.A1, U38.A9, U38.B2, U38.B8, U38.E4, U38.E5, U38.F4, U38.F5, U38.K2, U38.K3, U38.K5, U38.K7, U38.K8, U38.L1, U38.L9, U38.M1, U38.M2, U38.M8, U38.M9, U39.1, U39.4, U39.6, U39.9, U40.2, U40.PAD, USBSHLD7.1
GND8: C97.2, C98.2, C99.2, C100.2, C101.2, C102.2, C103.2, C104.2, C105.2, C106.2, C107.2, C108.2, D51.C, D52.C, D53.2, D54.GND, J49.1, J50.1, J51.GND, J51.GND2, J52.25, J53.6, J53.GND1, J53.GND2, J53.GND3, J53.GND4, J53.GND5, J53.GND6, J54.3, J54.5, J54.9, Q45.2, R201.1, R203.1, R208.1, R209.1, R210.1, R211.2, R213.1, R224.2, S25.3, S25.4, S27.3, S27.4, U41.2, U42.2, U43.A1, U43.A9, U43.B2, U43.B8, U43.E4, U43.E5, U43.F4, U43.F5, U43.K2, U43.K3, U43.K5, U43.K7, U43.K8, U43.L1, U43.L9, U43.M1, U43.M2, U43.M8, U43.M9, U44.1, U44.4, U44.6, U44.9, U45.2, U45.PAD, USBSHLD8.1
GND9: C109.2, C110.2, C111.2, C112.2, C113.2, C114.2, C115.2, C116.2, C117.2, C118.2, C119.2, C120.2, D57.C, D58.C, D59.2, D60.GND, J55.1, J56.1, J57.GND, J57.GND2, J58.25, J59.6, J59.GND1, J59.GND2, J59.GND3, J59.GND4, J59.GND5, J59.GND6, J60.3, J60.5, J60.9, Q50.2, R226.1, R228.1, R233.1, R234.1, R235.1, R236.2, R238.1, R249.2, S28.3, S28.4, S30.3, S30.4, U46.2, U47.2, U48.A1, U48.A9, U48.B2, U48.B8, U48.E4, U48.E5, U48.F4, U48.F5, U48.K2, U48.K3, U48.K5, U48.K7, U48.K8, U48.L1, U48.L9, U48.M1, U48.M2, U48.M8, U48.M9, U49.1, U49.4, U49.6, U49.9, U50.2, U50.PAD, USBSHLD9.1
GND10: C121.2, C122.2, C123.2, C124.2, C125.2, C126.2, C127.2, C128.2, C129.2, C130.2, C131.2, C132.2, D63.C, D64.C, D65.2, D66.GND, J61.1, J62.1, J63.GND, J63.GND2, J64.25, J65.6, J65.GND1, J65.GND2, J65.GND3, J65.GND4, J65.GND5, J65.GND6, J66.3, J66.5, J66.9, Q55.2, R251.1, R253.1, R258.1, R259.1, R260.1, R261.2, R263.1, R274.2, S31.3, S31.4, S33.3, S33.4, U51.2, U52.2, U53.A1, U53.A9, U53.B2, U53.B8, U53.E4, U53.E5, U53.F4, U53.F5, U53.K2, U53.K3, U53.K5, U53.K7, U53.K8, U53.L1, U53.L9, U53.M1, U53.M2, U53.M8, U53.M9, U54.1, U54.4, U54.6, U54.9, U55.2, U55.PAD, USBSHLD10.1
GND11: C133.2, C134.2, C135.2, C136.2, C137.2, C138.2, C139.2, C140.2, C141.2, C142.2, C143.2, C144.2, D69.C, D70.C, D71.2, D72.GND, J67.1, J68.1, J69.GND, J69.GND2, J70.25, J71.6, J71.GND1, J71.GND2, J71.GND3, J71.GND4, J71.GND5, J71.GND6, J72.3, J72.5, J72.9, Q60.2, R276.1, R278.1, R283.1, R284.1, R285.1, R286.2, R288.1, R299.2, S34.3, S34.4, S36.3, S36.4, U56.2, U57.2, U58.A1, U58.A9, U58.B2, U58.B8, U58.E4, U58.E5, U58.F4, U58.F5, U58.K2, U58.K3, U58.K5, U58.K7, U58.K8, U58.L1, U58.L9, U58.M1, U58.M2, U58.M8, U58.M9, U59.1, U59.4, U59.6, U59.9, U60.2, U60.PAD, USBSHLD11.1
unnamed: R1.2, U6.9
unnamed: D3.A, R4.2
unnamed: Q2.5, R17.2
unnamed: R5.1, R9.2, U6.8
unnamed: Q2.2, R18.2
unnamed: CHG.1, D1.C
unnamed: Q1.1, R10.2
unnamed: R15.2, S2.3, S2.4
unnamed: CUR.2, U4.5
unnamed: D5.DI, JP1.2
unnamed: CUR.1, R13.1
unnamed: LED.2, R2.1
unnamed: CUR.3, R6.2
unnamed: D4.A, R2.2
unnamed: D6.6, U6.3
unnamed: D6.1, J5.A6, J5.B6
unnamed: D1.A, R3.2
unnamed: D6.4, U6.4
unnamed: D6.3, J5.A7, J5.B7
unnamed: I2C.3, R28.2
unnamed: I2C.1, R29.2
unnamed: JP2.2, R4.1
unnamed: D2.C, MEAS.1, MEAS.3, Q1.2
unnamed: Q3.1, R14.2
unnamed: C5.1, J4.4, Q3.3, R16.1
unnamed: R14.1, R19.2, SDPC.2
unnamed: Q5.3, R20.2, R21.2
unnamed: C8.1, D5.VCC, JP3.2
unnamed: C2.1, C3.1, Q4.3, R1.1, U6.5, U6.6, U6.7
unnamed: Q4.1, R21.1
unnamed: Q5.1, R23.2
unnamed: R22.1, SDPC.3
unnamed: D8.A, R25.2
unnamed: R27.2, U10.9
unnamed: D9.A, R30.2
unnamed: R32.1, R33.2, U10.8
unnamed: CUR1.2, U2.5
unnamed: CUR1.1, R36.1
unnamed: CUR1.3, R26.2
unnamed: Q6.1, R37.2
unnamed: R38.2, S5.3, S5.4
unnamed: Q7.5, R39.2
unnamed: Q7.2, R40.2
unnamed: LED1.2, R41.1
unnamed: D10.A, R41.2
unnamed: D11.6, U10.3
unnamed: D11.1, J9.A6, J9.B6
unnamed: D11.4, U10.4
unnamed: D11.3, J9.A7, J9.B7
unnamed: CHG1.1, D8.C
unnamed: D12.DI, JP4.2
unnamed: I2C1.3, R42.2
unnamed: I2C1.1, R43.2
unnamed: JP5.2, R30.1
unnamed: D7.C, MEAS1.1, MEAS1.3, Q6.2
unnamed: Q8.1, R44.2
unnamed: C21.1, J11.4, Q8.3, R46.1
unnamed: R44.1, R45.2, SDPC1.2
unnamed: Q10.3, R47.2, R48.2
unnamed: C17.1, C18.1, Q9.3, R27.1, U10.5, U10.6, U10.7
unnamed: C22.1, D12.VCC, JP6.2
unnamed: Q9.1, R48.1
unnamed: R49.1, SDPC1.3
unnamed: Q10.1, R50.2
unnamed: D14.A, R52.2
unnamed: R54.2, U15.9
unnamed: D15.A, R55.2
unnamed: R57.1, R58.2, U15.8
unnamed: CUR2.2, U11.5
unnamed: CUR2.1, R61.1
unnamed: CUR2.3, R53.2
unnamed: Q11.1, R62.2
unnamed: R63.2, S8.3, S8.4
unnamed: Q12.5, R64.2
unnamed: Q12.2, R65.2
unnamed: LED2.2, R66.1
unnamed: D16.A, R66.2
unnamed: D17.6, U15.3
unnamed: D17.1, J15.A6, J15.B6
unnamed: D17.4, U15.4
unnamed: D17.3, J15.A7, J15.B7
unnamed: CHG2.1, D14.C
unnamed: D18.DI, JP7.2
unnamed: I2C2.3, R67.2
unnamed: I2C2.1, R68.2
unnamed: JP8.2, R55.1
unnamed: D13.C, MEAS2.1, MEAS2.3, Q11.2
unnamed: Q13.1, R69.2
unnamed: C33.1, J17.4, Q13.3, R71.1
unnamed: R69.1, R70.2, SDPC2.2
unnamed: Q15.3, R72.2, R73.2
unnamed: C30.1, C31.1, Q14.3, R54.1, U15.5, U15.6, U15.7
unnamed: C34.1, D18.VCC, JP9.2
unnamed: Q14.1, R73.1
unnamed: R74.1, SDPC2.3
unnamed: Q15.1, R75.2
unnamed: D20.A, R77.2
unnamed: R79.2, U20.9
unnamed: D21.A, R80.2
unnamed: R82.1, R83.2, U20.8
unnamed: CUR3.2, U16.5
unnamed: CUR3.1, R86.1
unnamed: CUR3.3, R78.2
unnamed: Q16.1, R87.2
unnamed: R88.2, S11.3, S11.4
unnamed: Q17.5, R89.2
unnamed: Q17.2, R90.2
unnamed: LED3.2, R91.1
unnamed: D22.A, R91.2
unnamed: D23.6, U20.3
unnamed: D23.1, J21.A6, J21.B6
unnamed: D23.4, U20.4
unnamed: D23.3, J21.A7, J21.B7
unnamed: CHG3.1, D20.C
unnamed: D24.DI, JP10.2
unnamed: I2C3.3, R92.2
unnamed: I2C3.1, R93.2
unnamed: JP11.2, R80.1
unnamed: D19.C, MEAS3.1, MEAS3.3, Q16.2
unnamed: Q18.1, R94.2
unnamed: C45.1, J23.4, Q18.3, R96.1
unnamed: R94.1, R95.2, SDPC3.2
unnamed: Q20.3, R97.2, R98.2
unnamed: C42.1, C43.1, Q19.3, R79.1, U20.5, U20.6, U20.7
unnamed: C46.1, D24.VCC, JP12.2
unnamed: Q19.1, R98.1
unnamed: R99.1, SDPC3.3
unnamed: Q20.1, R100.2
unnamed: D26.A, R102.2
unnamed: R104.2, U25.9
unnamed: D27.A, R105.2
unnamed: R107.1, R108.2, U25.8
unnamed: CUR4.2, U21.5
unnamed: CUR4.1, R111.1
unnamed: CUR4.3, R103.2
unnamed: Q21.1, R112.2
unnamed: R113.2, S14.3, S14.4
unnamed: Q22.5, R114.2
unnamed: Q22.2, R115.2
unnamed: LED4.2, R116.1
unnamed: D28.A, R116.2
unnamed: D29.6, U25.3
unnamed: D29.1, J27.A6, J27.B6
unnamed: D29.4, U25.4
unnamed: D29.3, J27.A7, J27.B7
unnamed: CHG4.1, D26.C
unnamed: D30.DI, JP13.2
unnamed: I2C4.3, R117.2
unnamed: I2C4.1, R118.2
unnamed: JP14.2, R105.1
unnamed: D25.C, MEAS4.1, MEAS4.3, Q21.2
unnamed: Q23.1, R119.2
unnamed: C57.1, J29.4, Q23.3, R121.1
unnamed: R119.1, R120.2, SDPC4.2
unnamed: Q25.3, R122.2, R123.2
unnamed: C54.1, C55.1, Q24.3, R104.1, U25.5, U25.6, U25.7
unnamed: C58.1, D30.VCC, JP15.2
unnamed: Q24.1, R123.1
unnamed: R124.1, SDPC4.3
unnamed: Q25.1, R125.2
unnamed: D32.A, R127.2
unnamed: R129.2, U30.9
unnamed: D33.A, R130.2
unnamed: R132.1, R133.2, U30.8
unnamed: CUR5.2, U26.5
unnamed: CUR5.1, R136.1
unnamed: CUR5.3, R128.2
unnamed: Q26.1, R137.2
unnamed: R138.2, S17.3, S17.4
unnamed: Q27.5, R139.2
unnamed: Q27.2, R140.2
unnamed: LED5.2, R141.1
unnamed: D34.A, R141.2
unnamed: D35.6, U30.3
unnamed: D35.1, J33.A6, J33.B6
unnamed: D35.4, U30.4
unnamed: D35.3, J33.A7, J33.B7
unnamed: CHG5.1, D32.C
unnamed: D36.DI, JP16.2
unnamed: I2C5.3, R142.2
unnamed: I2C5.1, R143.2
unnamed: JP17.2, R130.1
unnamed: D31.C, MEAS5.1, MEAS5.3, Q26.2
unnamed: Q28.1, R144.2
unnamed: C69.1, J35.4, Q28.3, R146.1
unnamed: R144.1, R145.2, SDPC5.2
unnamed: Q30.3, R147.2, R148.2
unnamed: C66.1, C67.1, Q29.3, R129.1, U30.5, U30.6, U30.7
unnamed: C70.1, D36.VCC, JP18.2
unnamed: Q29.1, R148.1
unnamed: R149.1, SDPC5.3
unnamed: Q30.1, R150.2
unnamed: D38.A, R152.2
unnamed: R154.2, U35.9
unnamed: D39.A, R155.2
unnamed: R157.1, R158.2, U35.8
unnamed: CUR6.2, U31.5
unnamed: CUR6.1, R161.1
unnamed: CUR6.3, R153.2
unnamed: Q31.1, R162.2
unnamed: R163.2, S20.3, S20.4
unnamed: Q32.5, R164.2
unnamed: Q32.2, R165.2
unnamed: LED6.2, R166.1
unnamed: D40.A, R166.2
unnamed: D41.6, U35.3
unnamed: D41.1, J39.A6, J39.B6
unnamed: D41.4, U35.4
unnamed: D41.3, J39.A7, J39.B7
unnamed: CHG6.1, D38.C
unnamed: D42.DI, JP19.2
unnamed: I2C6.3, R167.2
unnamed: I2C6.1, R168.2
unnamed: JP20.2, R155.1
unnamed: D37.C, MEAS6.1, MEAS6.3, Q31.2
unnamed: Q33.1, R169.2
unnamed: C81.1, J41.4, Q33.3, R171.1
unnamed: R169.1, R170.2, SDPC6.2
unnamed: Q35.3, R172.2, R173.2
unnamed: C78.1, C79.1, Q34.3, R154.1, U35.5, U35.6, U35.7
unnamed: C82.1, D42.VCC, JP21.2
unnamed: Q34.1, R173.1
unnamed: R174.1, SDPC6.3
unnamed: Q35.1, R175.2
unnamed: D44.A, R177.2
unnamed: R179.2, U40.9
unnamed: D45.A, R180.2
unnamed: R182.1, R183.2, U40.8
unnamed: CUR7.2, U36.5
unnamed: CUR7.1, R186.1
unnamed: CUR7.3, R178.2
unnamed: Q36.1, R187.2
unnamed: R188.2, S23.3, S23.4
unnamed: Q37.5, R189.2
unnamed: Q37.2, R190.2
unnamed: LED7.2, R191.1
unnamed: D46.A, R191.2
unnamed: D47.6, U40.3
unnamed: D47.1, J45.A6, J45.B6
unnamed: D47.4, U40.4
unnamed: D47.3, J45.A7, J45.B7
unnamed: CHG7.1, D44.C
unnamed: D48.DI, JP22.2
unnamed: I2C7.3, R192.2
unnamed: I2C7.1, R193.2
unnamed: JP23.2, R180.1
unnamed: D43.C, MEAS7.1, MEAS7.3, Q36.2
unnamed: Q38.1, R194.2
unnamed: C93.1, J47.4, Q38.3, R196.1
unnamed: R194.1, R195.2, SDPC7.2
unnamed: Q40.3, R197.2, R198.2
unnamed: C90.1, C91.1, Q39.3, R179.1, U40.5, U40.6, U40.7
unnamed: C94.1, D48.VCC, JP24.2
unnamed: Q39.1, R198.1
unnamed: R199.1, SDPC7.3
unnamed: Q40.1, R200.2
unnamed: D50.A, R202.2
unnamed: R204.2, U45.9
unnamed: D51.A, R205.2
unnamed: R207.1, R208.2, U45.8
unnamed: CUR8.2, U41.5
unnamed: CUR8.1, R211.1
unnamed: CUR8.3, R203.2
unnamed: Q41.1, R212.2
unnamed: R213.2, S26.3, S26.4
unnamed: Q42.5, R214.2
unnamed: Q42.2, R215.2
unnamed: LED8.2, R216.1
unnamed: D52.A, R216.2
unnamed: D53.6, U45.3
unnamed: D53.1, J51.A6, J51.B6
unnamed: D53.4, U45.4
unnamed: D53.3, J51.A7, J51.B7
unnamed: CHG8.1, D50.C
unnamed: D54.DI, JP25.2
unnamed: I2C8.3, R217.2
unnamed: I2C8.1, R218.2
unnamed: JP26.2, R205.1
unnamed: D49.C, MEAS8.1, MEAS8.3, Q41.2
unnamed: Q43.1, R219.2
unnamed: C105.1, J53.4, Q43.3, R221.1
unnamed: R219.1, R220.2, SDPC8.2
unnamed: Q45.3, R222.2, R223.2
unnamed: C102.1, C103.1, Q44.3, R204.1, U45.5, U45.6, U45.7
unnamed: C106.1, D54.VCC, JP27.2
unnamed: Q44.1, R223.1
unnamed: R224.1, SDPC8.3
unnamed: Q45.1, R225.2
unnamed: D56.A, R227.2
unnamed: R229.2, U50.9
unnamed: D57.A, R230.2
unnamed: R232.1, R233.2, U50.8
unnamed: CUR9.2, U46.5
unnamed: CUR9.1, R236.1
unnamed: CUR9.3, R228.2
unnamed: Q46.1, R237.2
unnamed: R238.2, S29.3, S29.4
unnamed: Q47.5, R239.2
unnamed: Q47.2, R240.2
unnamed: LED9.2, R241.1
unnamed: D58.A, R241.2
unnamed: D59.6, U50.3
unnamed: D59.1, J57.A6, J57.B6
unnamed: D59.4, U50.4
unnamed: D59.3, J57.A7, J57.B7
unnamed: CHG9.1, D56.C
unnamed: D60.DI, JP28.2
unnamed: I2C9.3, R242.2
unnamed: I2C9.1, R243.2
unnamed: JP29.2, R230.1
unnamed: D55.C, MEAS9.1, MEAS9.3, Q46.2
unnamed: Q48.1, R244.2
unnamed: C117.1, J59.4, Q48.3, R246.1
unnamed: R244.1, R245.2, SDPC9.2
unnamed: Q50.3, R247.2, R248.2
unnamed: C114.1, C115.1, Q49.3, R229.1, U50.5, U50.6, U50.7
unnamed: C118.1, D60.VCC, JP30.2
unnamed: Q49.1, R248.1
unnamed: R249.1, SDPC9.3
unnamed: Q50.1, R250.2
unnamed: D62.A, R252.2
unnamed: R254.2, U55.9
unnamed: D63.A, R255.2
unnamed: R257.1, R258.2, U55.8
unnamed: CUR10.2, U51.5
unnamed: CUR10.1, R261.1
unnamed: CUR10.3, R253.2
unnamed: Q51.1, R262.2
unnamed: R263.2, S32.3, S32.4
unnamed: Q52.5, R264.2
unnamed: Q52.2, R265.2
unnamed: LED10.2, R266.1
unnamed: D64.A, R266.2
unnamed: D65.6, U55.3
unnamed: D65.1, J63.A6, J63.B6
unnamed: D65.4, U55.4
unnamed: D65.3, J63.A7, J63.B7
unnamed: CHG10.1, D62.C
unnamed: D66.DI, JP31.2
unnamed: I2C10.3, R267.2
unnamed: I2C10.1, R268.2
unnamed: JP32.2, R255.1
unnamed: D61.C, MEAS10.1, MEAS10.3, Q51.2
unnamed: Q53.1, R269.2
unnamed: C129.1, J65.4, Q53.3, R271.1
unnamed: R269.1, R270.2, SDPC10.2
unnamed: Q55.3, R272.2, R273.2
unnamed: C126.1, C127.1, Q54.3, R254.1, U55.5, U55.6, U55.7
unnamed: C130.1, D66.VCC, JP33.2
unnamed: Q54.1, R273.1
unnamed: R274.1, SDPC10.3
unnamed: Q55.1, R275.2
unnamed: D68.A, R277.2
unnamed: R279.2, U60.9
unnamed: D69.A, R280.2
unnamed: R282.1, R283.2, U60.8
unnamed: CUR11.2, U56.5
unnamed: CUR11.1, R286.1
unnamed: CUR11.3, R278.2
unnamed: Q56.1, R287.2
unnamed: R288.2, S35.3, S35.4
unnamed: Q57.5, R289.2
unnamed: Q57.2, R290.2
unnamed: LED11.2, R291.1
unnamed: D70.A, R291.2
unnamed: D71.6, U60.3
unnamed: D71.1, J69.A6, J69.B6
unnamed: D71.4, U60.4
unnamed: D71.3, J69.A7, J69.B7
unnamed: CHG11.1, D68.C
unnamed: D72.DI, JP34.2
unnamed: I2C11.3, R292.2
unnamed: I2C11.1, R293.2
unnamed: JP35.2, R280.1
unnamed: D67.C, MEAS11.1, MEAS11.3, Q56.2
unnamed: Q58.1, R294.2
unnamed: C141.1, J71.4, Q58.3, R296.1
unnamed: R294.1, R295.2, SDPC11.2
unnamed: Q60.3, R297.2, R298.2
unnamed: C138.1, C139.1, Q59.3, R279.1, U60.5, U60.6, U60.7
unnamed: C142.1, D72.VCC, JP36.2
unnamed: Q59.1, R298.1
unnamed: R299.1, SDPC11.3
unnamed: Q60.1, R300.2
PA1: J10.4, JP4.1, U8.J9
PA2: J10.3, U8.J8
PA3: J10.6, U8.H9
PA4: J10.5, U8.H8
PA5: J10.21, S6.1, S6.2, U8.B1
PA6: J10.20, U8.B3
PA7: J16.4, JP7.1, U13.J9
PA7/UART-LOG-TXD: J1.22, Q2.6, S2.1, S2.2, U1.A5, U6.20
PA7/UART-LOG-TXD1: J10.22, Q7.6, S5.1, S5.2, U8.A5, U10.20
PA7/UART-LOG-TXD2: J16.22, Q12.6, S8.1, S8.2, U13.A5, U15.20
PA7/UART-LOG-TXD3: J22.22, Q17.6, S11.1, S11.2, U18.A5, U20.20
PA7/UART-LOG-TXD4: J28.22, Q22.6, S14.1, S14.2, U23.A5, U25.20
PA7/UART-LOG-TXD5: J34.22, Q27.6, S17.1, S17.2, U28.A5, U30.20
PA7/UART-LOG-TXD6: J40.22, Q32.6, S20.1, S20.2, U33.A5, U35.20
PA7/UART-LOG-TXD7: J46.22, Q37.6, S23.1, S23.2, U38.A5, U40.20
PA7/UART-LOG-TXD8: J52.22, Q42.6, S26.1, S26.2, U43.A5, U45.20
PA7/UART-LOG-TXD9: J58.22, Q47.6, S29.1, S29.2, U48.A5, U50.20
PA7/UART-LOG-TXD10: J64.22, Q52.6, S32.1, S32.2, U53.A5, U55.20
PA7/UART-LOG-TXD11: J70.22, Q57.6, S35.1, S35.2, U58.A5, U60.20
PA8: J16.3, U13.J8
PA8/UART-LOG-RXD: J1.23, U1.A6, U6.21
PA8/UART-LOG-RXD1: J10.23, U8.A6, U10.21
PA8/UART-LOG-RXD2: J16.23, U13.A6, U15.21
PA8/UART-LOG-RXD3: J22.23, U18.A6, U20.21
PA8/UART-LOG-RXD4: J28.23, U23.A6, U25.21
PA8/UART-LOG-RXD5: J34.23, U28.A6, U30.21
PA8/UART-LOG-RXD6: J40.23, U33.A6, U35.21
PA8/UART-LOG-RXD7: J46.23, U38.A6, U40.21
PA8/UART-LOG-RXD8: J52.23, U43.A6, U45.21
PA8/UART-LOG-RXD9: J58.23, U48.A6, U50.21
PA8/UART-LOG-RXD10: J64.23, U53.A6, U55.21
PA8/UART-LOG-RXD11: J70.23, U58.A6, U60.21
PA9: J16.6, U13.H9
PA10: J16.5, U13.H8
PA11: J16.21, S9.1, S9.2, U13.B1
PA12: J1.4, JP1.1, U1.J9
PA13: J1.3, U1.J8
PA14: J1.6, U1.H9
PA15: J1.5, U1.H8
PA16: J16.20, U13.B3
PA17: J22.4, JP10.1, U18.J9
PA18: J22.3, U18.J8
PA19: J22.6, U18.H9
PA20: J22.5, U18.H8
PA21: J22.21, S12.1, S12.2, U18.B1
PA22: J22.20, U18.B3
PA23: J28.4, JP13.1, U23.J9
PA24: J28.3, U23.J8
PA25: J28.6, U23.H9
PA25/SCL: J1.2, J3.4, R28.1, U1.C2, U5.7
PA25/SCL1: J8.4, J10.2, R42.1, U8.C2, U9.7
PA25/SCL2: J14.4, J16.2, R67.1, U13.C2, U14.7
PA25/SCL3: J20.4, J22.2, R92.1, U18.C2, U19.7
PA25/SCL4: J26.4, J28.2, R117.1, U23.C2, U24.7
PA25/SCL5: J32.4, J34.2, R142.1, U28.C2, U29.7
PA25/SCL6: J38.4, J40.2, R167.1, U33.C2, U34.7
PA25/SCL7: J44.4, J46.2, R192.1, U38.C2, U39.7
PA25/SCL8: J50.4, J52.2, R217.1, U43.C2, U44.7
PA25/SCL9: J56.4, J58.2, R242.1, U48.C2, U49.7
PA25/SCL10: J62.4, J64.2, R267.1, U53.C2, U54.7
PA25/SCL11: J68.4, J70.2, R292.1, U58.C2, U59.7
PA26: J28.5, U23.H8
PA26/SDA: J1.1, J3.3, R29.1, U1.C1, U5.8
PA26/SDA1: J8.3, J10.1, R43.1, U8.C1, U9.8
PA26/SDA2: J14.3, J16.1, R68.1, U13.C1, U14.8
PA26/SDA3: J20.3, J22.1, R93.1, U18.C1, U19.8
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
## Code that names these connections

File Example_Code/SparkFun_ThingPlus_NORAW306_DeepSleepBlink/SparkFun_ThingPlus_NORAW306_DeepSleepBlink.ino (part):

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    //printf("\r\nDeep sleep wakeuped! \r\n");
    uint32_t wakereason_number = PowerSave.AONWakeReason();

    //pinMode(17, OUTPUT); // 17 SDPC uSD power control
    //digitalWrite(17, LOW); // Turn on uSD power if you'd like to measure its current consumption   
    
    if (wakereason_number == AONWakeReason_AON_GPIO) {
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        delay(5000);
    }

    //pinMode(17, INPUT_PULLUP); // 17 SDPC uSD power control (Pullup = off)

    PowerSave.AONWakeClear();
}
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
    pinMode(0, INPUT_PULLDOWN); // LOG RX, can backpower the CP2102
    pinMode(1, INPUT_PULLDOWN); // LOG TX, can backpower the CP2102
    pinMode(4, INPUT_PULLDOWN); // SPI0_CS, can sink current from 3V3 via R16 (100K), note, this is only possible if you leave uSD power on
    pinMode(5, INPUT_PULLDOWN); // SPI0_CLK
    pinMode(6, INPUT_PULLDOWN); // SPI0_PICO
    pinMode(7, INPUT_PULLDOWN); // SPI0_POCI

    pinMode(11, INPUT_PULLUP); // SDA
    pinMode(12, INPUT_PULLUP); // SCL
    pinMode(17, INPUT_PULLUP); // 17 SDPC uSD power control
    pinMode(20, INPUT_PULLNONE); // aka PB_24, this is tied internally to PB_23 (aka Arduino pin "17") and also defaults to internal pulldown.

    PowerSave.begin(DEEPSLEEP_MODE);
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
